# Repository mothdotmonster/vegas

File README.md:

# VEGAS

Point of sale inspired keyboard with a unique layout.

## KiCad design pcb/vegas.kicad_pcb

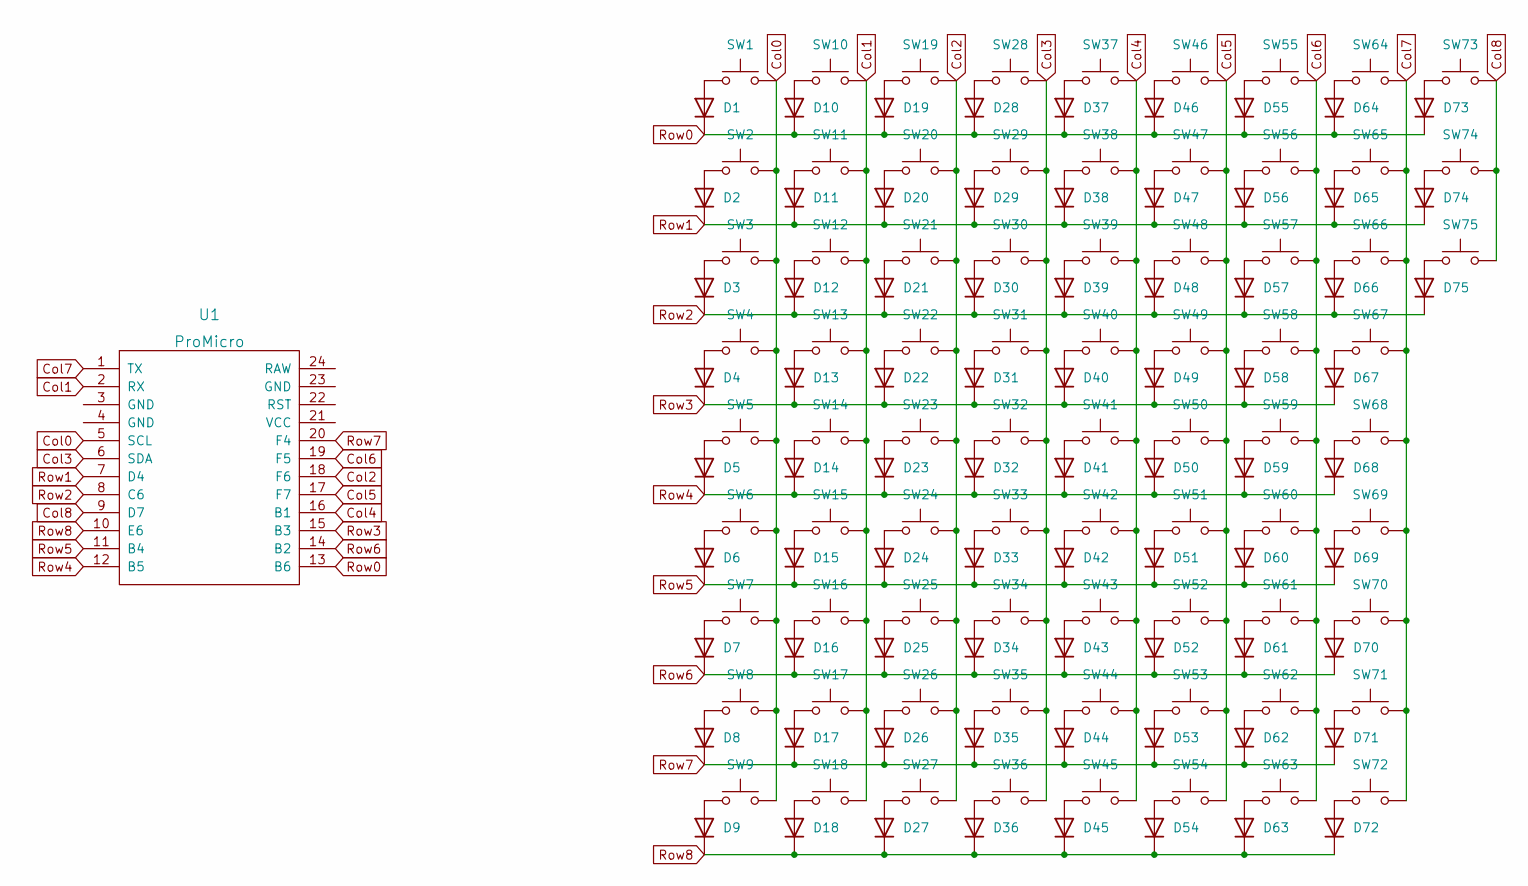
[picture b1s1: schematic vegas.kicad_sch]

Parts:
D1, D2, D3, D4, D5, D6, D7, D8, D9, D10, D11, D12, D13, D14, D15, D16, D17, D18, D19, D20, D21, D22, D23, D24, D25, D26, D27, D28, D29, D30, D31, D32, D33, D34, D35, D36, D37, D38, D39, D40, D41, D42, D43, D44, D45, D46, D47, D48, D49, D50, D51, D52, D53, D54, D55, D56, D57, D58, D59, D60, D61, D62, D63, D64, D65, D66, D67, D68, D69, D70, D71, D72, D73, D74, D75: 1N4148W; D_SOD-123; JLC C81598
SW1, SW2, SW3, SW4, SW5, SW6, SW7, SW8, SW9, SW10, SW11, SW12, SW13, SW14, SW15, SW16, SW17, SW18, SW19, SW20, SW21, SW22, SW23, SW24, SW25, SW26, SW27, SW28, SW29, SW30, SW31, SW32, SW33, SW34, SW35, SW36, SW37, SW38, SW39, SW40, SW41, SW42, SW43, SW44, SW45, SW46, SW47, SW48, SW49, SW50, SW51, SW52, SW53, SW54, SW55, SW56, SW57, SW58, SW59, SW60, SW61, SW62, SW63, SW64, SW65, SW66, SW67, SW68, SW69, SW70, SW71, SW72, SW73, SW74, SW75: SW_Push; MX-Alps-Choc-1U-NoLED
U1: ProMicro; ArduinoProMicro

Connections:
Col0: SW1.2, SW2.2, SW3.2, SW4.2, SW5.2, SW6.2, SW7.2, SW8.2, SW9.2, U1.5 (SCL)
Col1: SW10.2, SW11.2, SW12.2, SW13.2, SW14.2, SW15.2, SW16.2, SW17.2, SW18.2, U1.2 (RX)
Col2: SW19.2, SW20.2, SW21.2, SW22.2, SW23.2, SW24.2, SW25.2, SW26.2, SW27.2, U1.18 (F6)
Col3: SW28.2, SW29.2, SW30.2, SW31.2, SW32.2, SW33.2, SW34.2, SW35.2, SW36.2, U1.6 (SDA)
Col4: SW37.2, SW38.2, SW39.2, SW40.2, SW41.2, SW42.2, SW43.2, SW44.2, SW45.2, U1.16 (B1)
Col5: SW46.2, SW47.2, SW48.2, SW49.2, SW50.2, SW51.2, SW52.2, SW53.2, SW54.2, U1.17 (F7)
Col6: SW55.2, SW56.2, SW57.2, SW58.2, SW59.2, SW60.2, SW61.2, SW62.2, SW63.2, U1.19 (F5)
Col7: SW64.2, SW65.2, SW66.2, SW67.2, SW68.2, SW69.2, SW70.2, SW71.2, SW72.2, U1.1 (TX)
Col8: SW73.2, SW74.2, SW75.2, U1.9 (D7)
unnamed: D1.2 (A), SW1.1
unnamed: D2.2 (A), SW2.1
unnamed: D3.2 (A), SW3.1
unnamed: D4.2 (A), SW4.1
unnamed: D5.2 (A), SW5.1
unnamed: D6.2 (A), SW6.1
unnamed: D7.2 (A), SW7.1
unnamed: D8.2 (A), SW8.1
unnamed: D9.2 (A), SW9.1
unnamed: D10.2 (A), SW10.1
unnamed: D11.2 (A), SW11.1
unnamed: D12.2 (A), SW12.1
unnamed: D13.2 (A), SW13.1
unnamed: D14.2 (A), SW14.1
unnamed: D15.2 (A), SW15.1
unnamed: D16.2 (A), SW16.1
unnamed: D17.2 (A), SW17.1
unnamed: D18.2 (A), SW18.1
unnamed: D19.2 (A), SW19.1
unnamed: D20.2 (A), SW20.1
unnamed: D21.2 (A), SW21.1
unnamed: D22.2 (A), SW22.1
unnamed: D23.2 (A), SW23.1
unnamed: D24.2 (A), SW24.1
unnamed: D25.2 (A), SW25.1
unnamed: D26.2 (A), SW26.1
unnamed: D27.2 (A), SW27.1
unnamed: D28.2 (A), SW28.1
unnamed: D29.2 (A), SW29.1
unnamed: D30.2 (A), SW30.1
unnamed: D31.2 (A), SW31.1
unnamed: D32.2 (A), SW32.1
unnamed: D33.2 (A), SW33.1
unnamed: D34.2 (A), SW34.1
unnamed: D35.2 (A), SW35.1
unnamed: D36.2 (A), SW36.1
unnamed: D37.2 (A), SW37.1
unnamed: D38.2 (A), SW38.1
unnamed: D39.2 (A), SW39.1
unnamed: D40.2 (A), SW40.1
unnamed: D41.2 (A), SW41.1
unnamed: D42.2 (A), SW42.1
unnamed: D43.2 (A), SW43.1
unnamed: D44.2 (A), SW44.1
unnamed: D45.2 (A), SW45.1
unnamed: D46.2 (A), SW46.1
unnamed: D47.2 (A), SW47.1
unnamed: D48.2 (A), SW48.1
unnamed: D49.2 (A), SW49.1
unnamed: D50.2 (A), SW50.1
unnamed: D51.2 (A), SW51.1
unnamed: D52.2 (A), SW52.1
unnamed: D53.2 (A), SW53.1
unnamed: D54.2 (A), SW54.1
unnamed: D55.2 (A), SW55.1
unnamed: D56.2 (A), SW56.1
unnamed: D57.2 (A), SW57.1
unnamed: D58.2 (A), SW58.1
unnamed: D59.2 (A), SW59.1
unnamed: D60.2 (A), SW60.1
unnamed: D61.2 (A), SW61.1
unnamed: D62.2 (A), SW62.1
unnamed: D63.2 (A), SW63.1
unnamed: D64.2 (A), SW64.1
unnamed: D65.2 (A), SW65.1
unnamed: D66.2 (A), SW66.1
unnamed: D67.2 (A), SW67.1
unnamed: D68.2 (A), SW68.1
unnamed: D69.2 (A), SW69.1
unnamed: D70.2 (A), SW70.1
unnamed: D71.2 (A), SW71.1
unnamed: D72.2 (A), SW72.1
unnamed: D73.2 (A), SW73.1
unnamed: D74.2 (A), SW74.1
unnamed: D75.2 (A), SW75.1
Row0: D1.1 (K), D10.1 (K), D19.1 (K), D28.1 (K), D37.1 (K), D46.1 (K), D55.1 (K), D64.1 (K), D73.1 (K), U1.13 (B6)
Row1: D2.1 (K), D11.1 (K), D20.1 (K), D29.1 (K), D38.1 (K), D47.1 (K), D56.1 (K), D65.1 (K), D74.1 (K), U1.7 (D4)
Row2: D3.1 (K), D12.1 (K), D21.1 (K), D30.1 (K), D39.1 (K), D48.1 (K), D57.1 (K), D66.1 (K), D75.1 (K), U1.8 (C6)
Row3: D4.1 (K), D13.1 (K), D22.1 (K), D31.1 (K), D40.1 (K), D49.1 (K), D58.1 (K), D67.1 (K), U1.15 (B3)
Row4: D5.1 (K), D14.1 (K), D23.1 (K), D32.1 (K), D41.1 (K), D50.1 (K), D59.1 (K), D68.1 (K), U1.12 (B5)
Row5: D6.1 (K), D15.1 (K), D24.1 (K), D33.1 (K), D42.1 (K), D51.1 (K), D60.1 (K), D69.1 (K), U1.11 (B4)
Row6: D7.1 (K), D16.1 (K), D25.1 (K), D34.1 (K), D43.1 (K), D52.1 (K), D61.1 (K), D70.1 (K), U1.14 (B2)
Row7: D8.1 (K), D17.1 (K), D26.1 (K), D35.1 (K), D44.1 (K), D53.1 (K), D62.1 (K), D71.1 (K), U1.20 (F4)
Row8: D9.1 (K), D18.1 (K), D27.1 (K), D36.1 (K), D45.1 (K), D54.1 (K), D63.1 (K), D72.1 (K), U1.10 (E6)

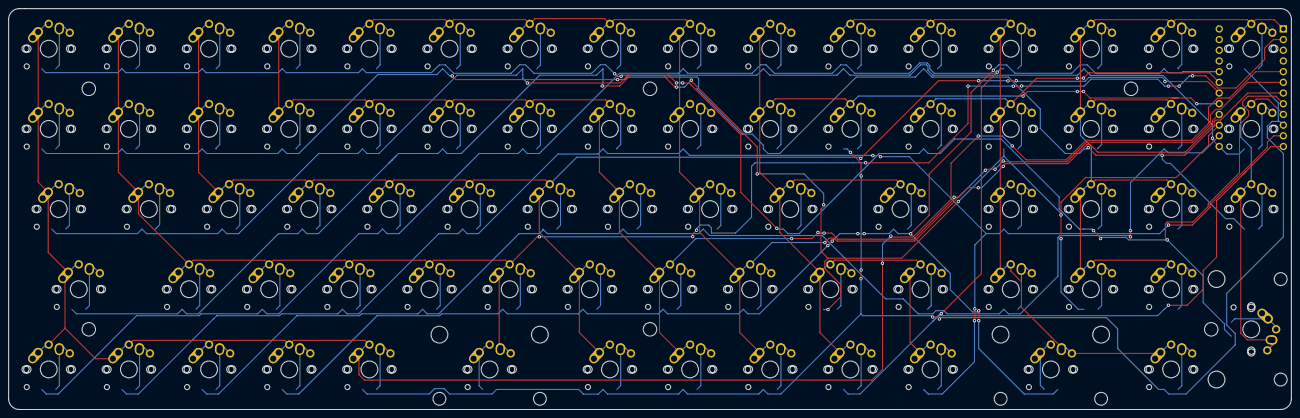
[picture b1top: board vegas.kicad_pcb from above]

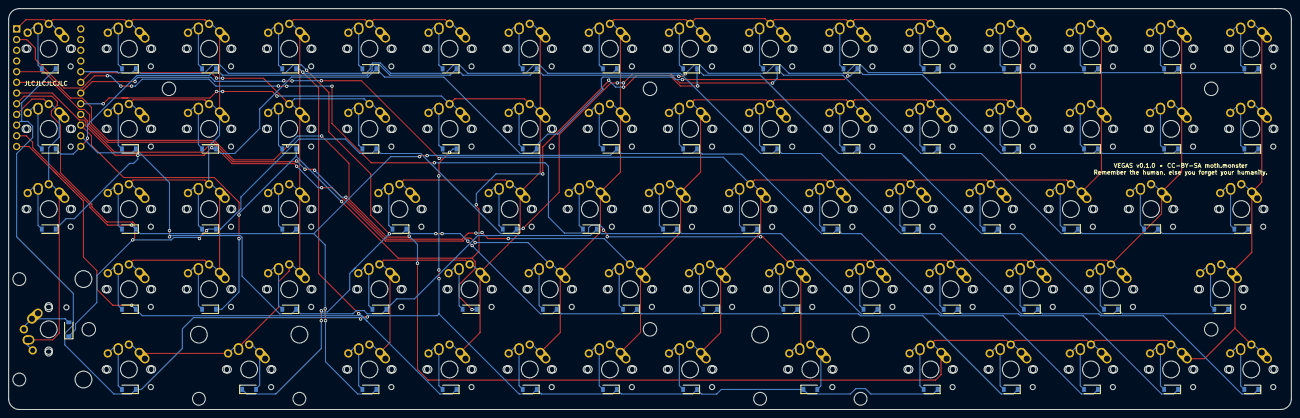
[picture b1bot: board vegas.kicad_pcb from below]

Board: 2 copper layers, 304.8 x 95.2 mm, 151 parts (76 on the bottom side), 93 nets.

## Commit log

2022-09-01 license
2022-09-01 initial design
2022-09-01 v0.1.0 final

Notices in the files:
pcb/vegas.kicad_pcb:
VEGAS v0.1.0 • CC-BY-SA moth.monster
